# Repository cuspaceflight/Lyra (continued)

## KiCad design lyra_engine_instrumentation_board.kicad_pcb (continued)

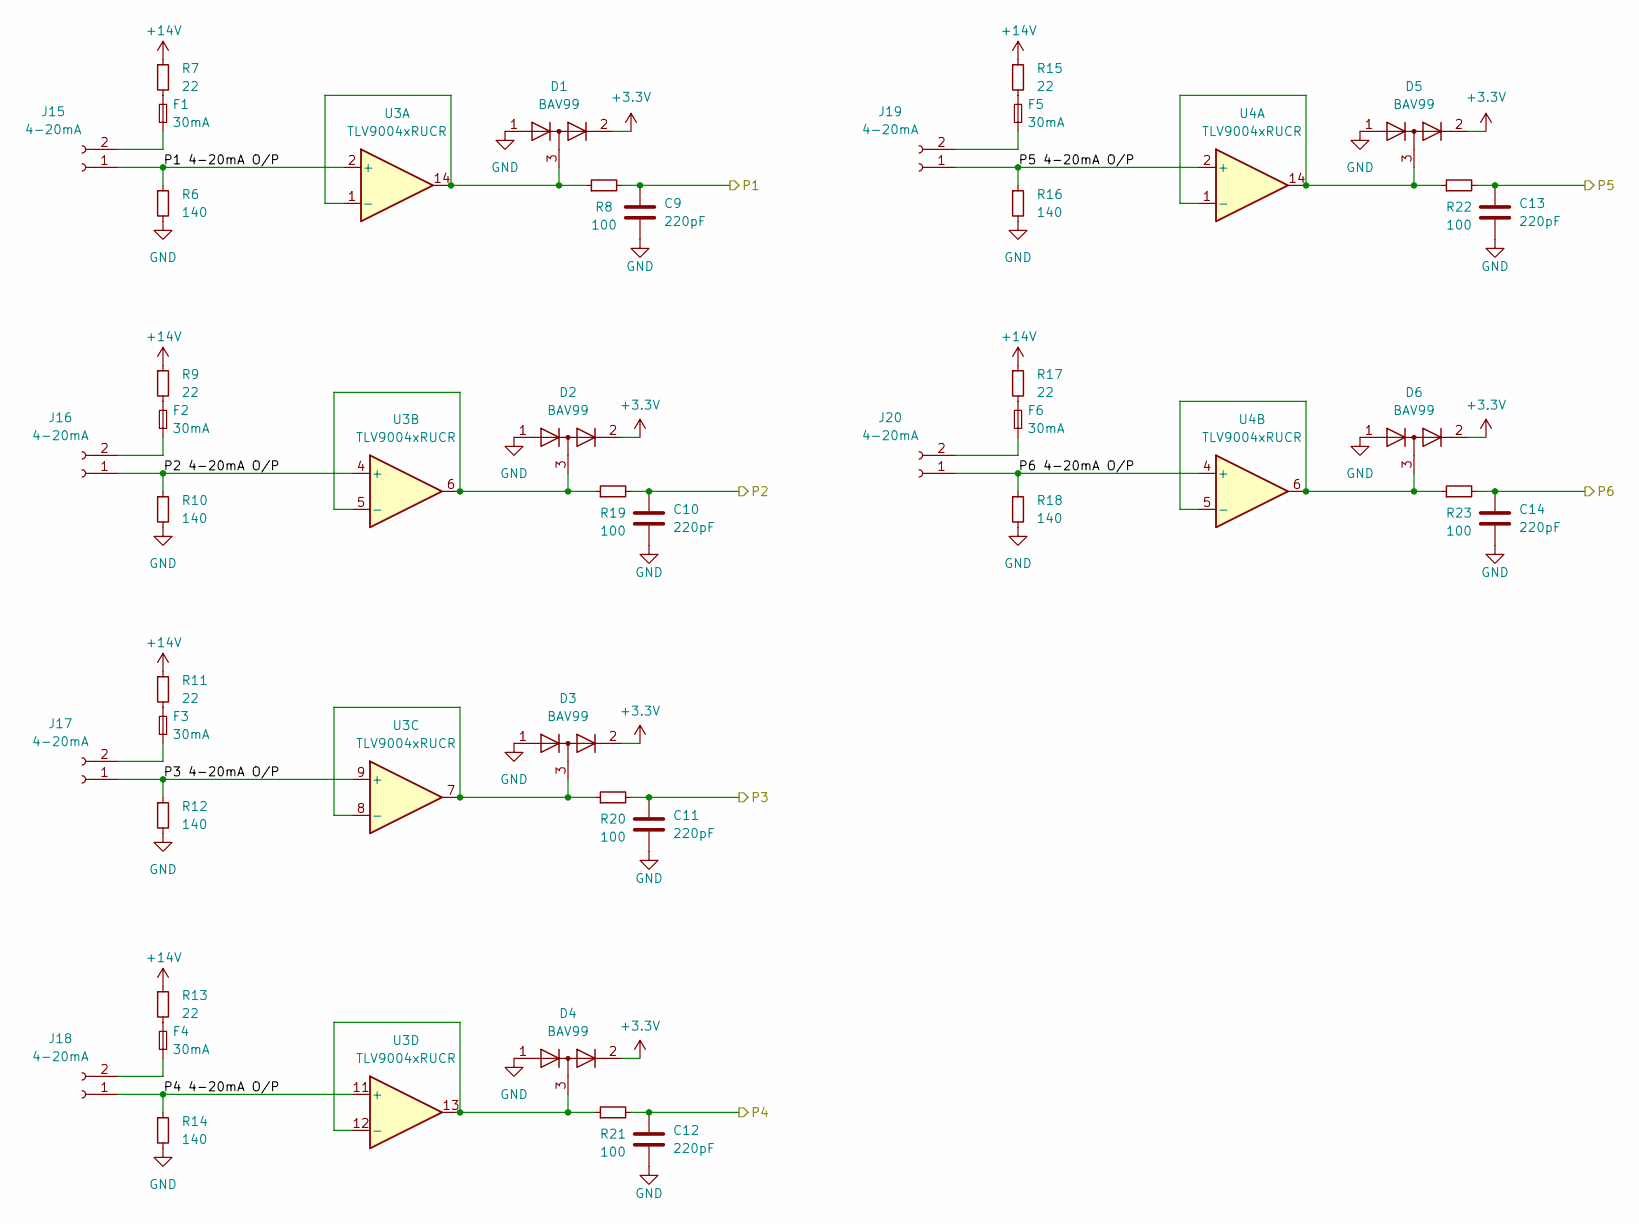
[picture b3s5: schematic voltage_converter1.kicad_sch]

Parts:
C9, C10, C11, C12, C13, C14: 220pF; Fuse_1206_3216Metric_Pad1.42x1.75mm_HandSolder
D1, D2, D3, D4, D5, D6: BAV99; SOT-23
F1, F2, F3, F4, F5, F6: 30mA; Fuse_1206_3216Metric_Pad1.42x1.75mm_HandSolder
J15, J16, J17, J18, J19, J20: 4-20mA; Molex_Nano-Fit_105309-xx02_1x02_P2.50mm_Vertical
R6, R10, R12, R14, R16, R18: 140; R_1206_3216Metric_Pad1.30x1.75mm_HandSolder
R7, R9, R11, R13, R15, R17: 22; R_1206_3216Metric_Pad1.30x1.75mm_HandSolder
R8, R19, R20, R21, R22, R23: 100; R_1206_3216Metric_Pad1.30x1.75mm_HandSolder
U3, U4: TLV9004xRUCR; Texas_S-PX2QFN-14

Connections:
+3.3V: D1.2 (A), D2.2 (A), D3.2 (A), D4.2 (A), D5.2 (A), D6.2 (A); also elsewhere on the board
+14V: R7.1, R9.1, R11.1, R13.1, R15.1, R17.1; also elsewhere on the board
/Pressure Inputs/P1: C9.2, R8.2; also elsewhere on the board
/Pressure Inputs/P1 4-20mA O/P: J15.1, R6.1, U3.2 (+)
/Pressure Inputs/P2: C10.2, R19.2; also elsewhere on the board
/Pressure Inputs/P2 4-20mA O/P: J16.1, R10.1, U3.4 (+)
/Pressure Inputs/P3: C11.2, R20.2; also elsewhere on the board
/Pressure Inputs/P3 4-20mA O/P: J17.1, R12.1, U3.9 (+)
/Pressure Inputs/P4: C12.2, R21.2; also elsewhere on the board
/Pressure Inputs/P4 4-20mA O/P: J18.1, R14.1, U3.11 (+)
/Pressure Inputs/P5: C13.2, R22.2; also elsewhere on the board
/Pressure Inputs/P5 4-20mA O/P: J19.1, R16.1, U4.2 (+)
/Pressure Inputs/P6: C14.2, R23.2; also elsewhere on the board
/Pressure Inputs/P6 4-20mA O/P: J20.1, R18.1, U4.4 (+)
GND: C9.1, C10.1, C11.1, C12.1, C13.1, C14.1, D1.1 (K), D2.1 (K), D3.1 (K), D4.1 (K), D5.1 (K), D6.1 (K), R6.2, R10.2, R12.2, R14.2, R16.2, R18.2; also elsewhere on the board
unnamed: F1.2, R7.2
unnamed: F2.2, R9.2
unnamed: F3.2, R11.2
unnamed: F4.2, R13.2
unnamed: F5.2, R15.2
unnamed: F6.2, R17.2
unnamed: F1.1, J15.2
unnamed: F2.1, J16.2
unnamed: F3.1, J17.2
unnamed: F4.1, J18.2
unnamed: F5.1, J19.2
unnamed: F6.1, J20.2
unnamed: D1.3 (K), R8.1, U3.1 (-), U3.14
unnamed: D2.3 (K), R19.1, U3.5 (-), U3.6
unnamed: D3.3 (K), R20.1, U3.7, U3.8 (-)
unnamed: D4.3 (K), R21.1, U3.12 (-), U3.13
unnamed: D5.3 (K), R22.1, U4.1 (-), U4.14
unnamed: D6.3 (K), R23.1, U4.5 (-), U4.6

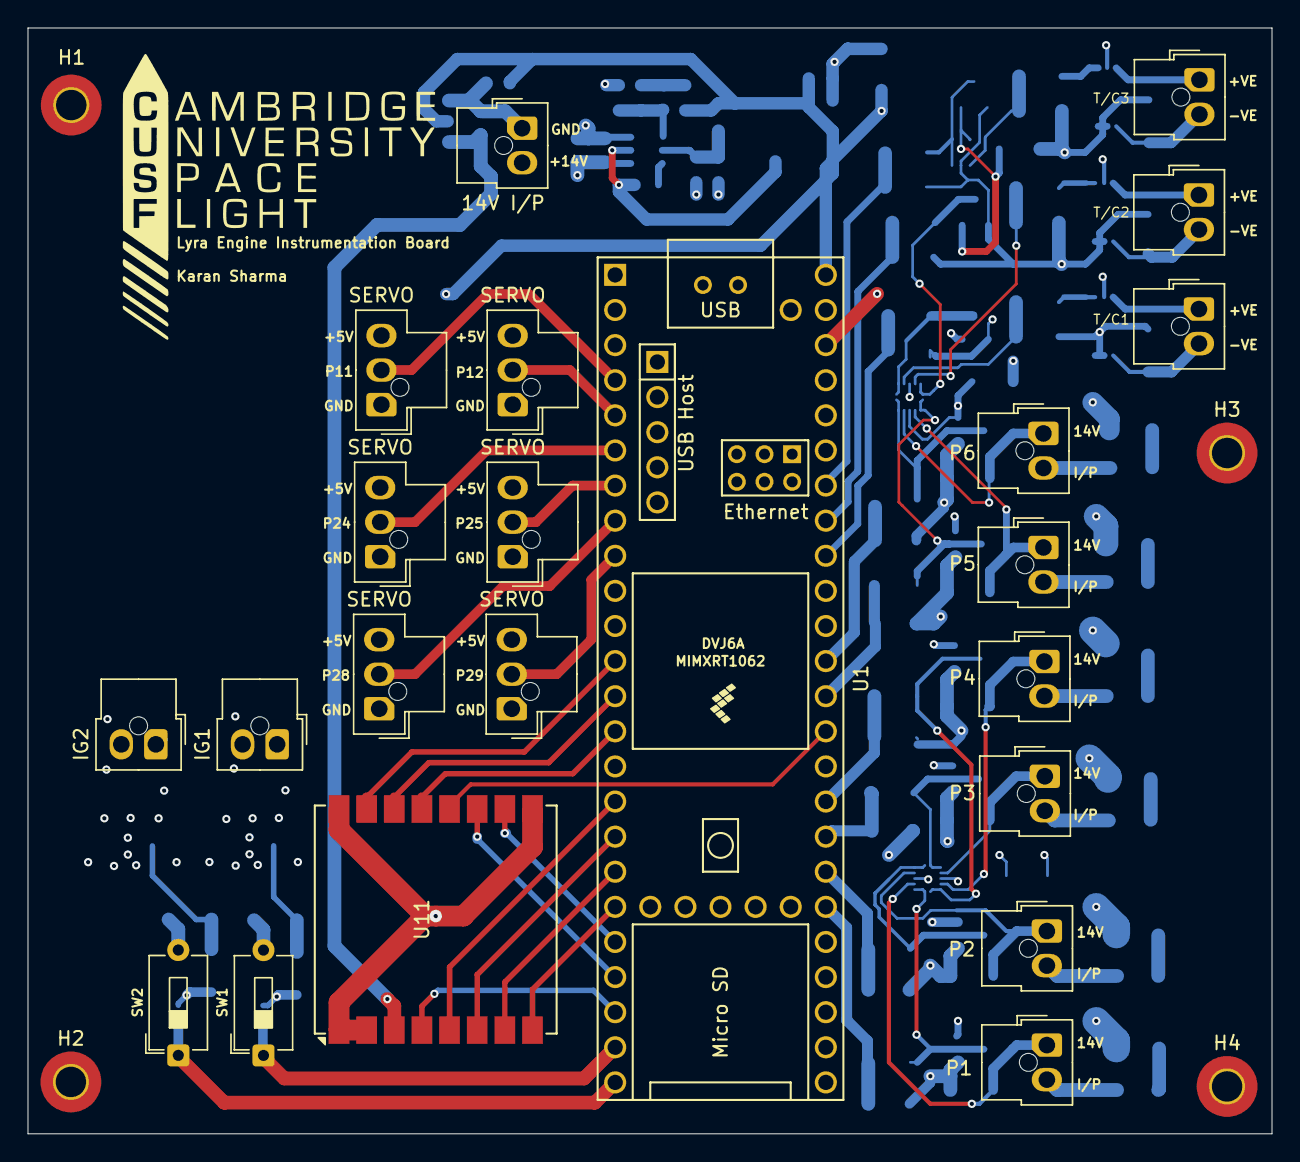
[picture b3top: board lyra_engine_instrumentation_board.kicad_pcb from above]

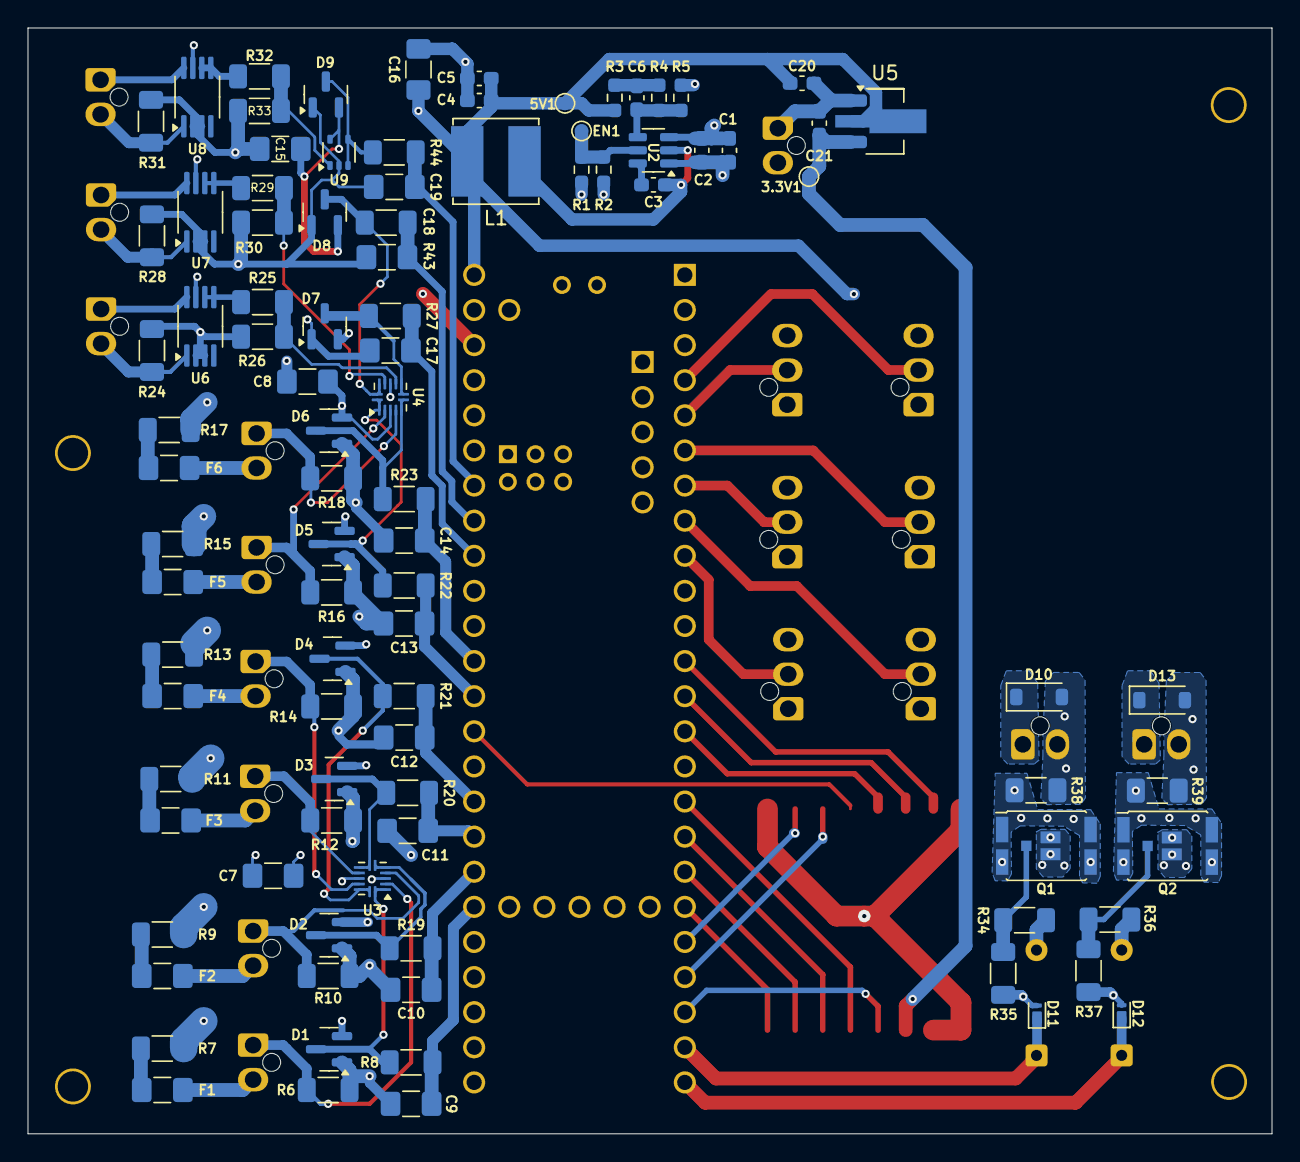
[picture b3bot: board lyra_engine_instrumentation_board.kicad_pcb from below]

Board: 4 copper layers, 90.0 x 80.0 mm, 121 parts (95 on the bottom side), 85 nets.

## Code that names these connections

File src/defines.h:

#pragma once

#define BMP_I2C_PORT i2c1
#define BMP_ADDR     0x76
#define BMP_SDA      6
#define BMP_SCL      7

#define ICM_SPI_PORT spi0
#define ICM_MISO     4
#define ICM_MOSI     3
#define ICM_CS       5
#define ICM_SCK      2

#define LORA_SPI_PORT spi1
#define LORA_MISO     12
#define LORA_MOSI     11
#define LORA_CS       9
#define LORA_SCK      10
#define LORA_BUSY     13
#define LORA_RST      8
#define LORA_DIO1     14

#define GPS_I2C  i2c0
#define GPS_SDA  16
#define GPS_SCL  17
#define GPS_ADDR 0x42

#define CONFIG_LORA_SF              LORA_SF_12
#define CONFIG_LORA_BW              LORA_BW_250
#define CONFIG_LORA_CR              LORA_CR_4_5
#define CONFIG_LORA_PREAMBLE        0x08
#define CONFIG_LORA_IMPLICIT_HEADER false
#define CONFIG_LORA_CRC             true
#define CONFIG_LORA_INVERT_IQ       false
#define CONFIG_LORA_POWER           14
#define CONFIG_LORA_RAMP_TIME       LORA_RAMP_TIME_200U

#define CONFIG_BMP_OSR_P BMP_OVERSAMPLE_X2
#define CONFIG_BMP_OSR_T BMP_OVERSAMPLE_X1
#define CONFIG_BMP_ODR   BMP_ODR_100
#define CONFIG_BMP_IIR   BMP_IIR_COEF_0

#define CONFIG_ICM_ACCEL_MODE ICM_PWR_LOW_NOISE
#define CONFIG_ICM_GYRO_MODE  ICM_PWR_LOW_NOISE
#define CONFIG_ICM_ACCEL_FSR  ICM_ACCEL_FSR_32g
#define CONFIG_ICM_ACCEL_ODR  ICM_ACCEL_ODR_2_KHZ
#define CONFIG_ICM_GYRO_FSR   ICM_GYRO_FSR_500
#define CONFIG_ICM_GYRO_ODR   ICM_GYRO_ODR_2_KHZ

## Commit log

2025-10-13 Board aligned with V2 on google drive, and around half of the code for Teensy
2025-10-13 Initial project
2025-11-15 Added files
2025-11-15 more updates
2026-01-06 Completed first revision of PCB
    Fully routed and checked in tolerance with JLCPCB manufacturing capabilities for 4L boards. Schematic needs checking and LCSC parts need assigning.
2026-01-25 Added local library
2026-01-25 added footprints and CAD model
2026-02-08 Initial minor fixes of routing
2026-02-25 update to KiCad v10
2026-03-26 new design
2026-04-10 fix PCB
2026-04-12 switched to RP2350A and added flash chip due to parts shortage
2026-05-03 Final manufactured version
2026-05-09 chore: working hello world
2026-05-10 feat: working BMP temperature and pressure reading
2026-05-10 refactor: move uint16_t and uint32_t combines into macros
2026-05-10 refactor: format
2026-05-10 feat: start implementing mpu
2026-05-10 refactor: rework bmp
2026-05-11 refactor: rename components
2026-05-11 feat: added sensor correction information for the icm
2026-05-11 chore: export compile_commands.json with nix build script
2026-05-11 refactor: move library code to separate folder
2026-05-11 feat: partially working lora tx implementation
2026-05-15 chore: remove compile_commands copying from flake.nix
2026-05-15 feat: working LoRa transmission
2026-05-15 refactor: cleanup icm code
2026-05-15 feat: add packet receiving to lora
2026-05-16 fix: bmp388 pressure reading wrong. Change to double instead of float
2026-05-16 feat: add examples directory
2026-05-16 example: add bmp388 example
2026-05-16 example: add ICM example
2026-05-16 example: add lora transmit example
2026-05-16 example: add lora receive example
2026-05-16 chore: update .gitignore
2026-05-17 feat: add logger
2026-05-17 feat: add logging to the BMP library
2026-05-17 feat: add logging to the ICM library
2026-05-17 feat: add logging to the SX126X library
2026-05-18 feat: add pseudo tasks that are executed at a set frequency
2026-05-22 feat: add struct transmitting for Velox
2026-05-22 feat: add gps NMEA passing for GNGLL
2026-05-23 feat: added GGA, GLL, and RMC passing for NMEA messages
2026-05-23 feat: add gps to main loop
2026-05-23 refactor: remove erroneous buffer from gps example
